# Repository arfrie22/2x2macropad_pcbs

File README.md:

# The PCBs for the 2x2 Macropad

This is a 2x2 Macropad with per-key RGB backlighting. It uses the RP2040 microcontroller and uses a custom firmware located at [https://github.com/arfrie22/2x2macropad_firmware](https://github.com/arfrie22/2x2macropad_firmware).

The PCBs are designed in KiCad

## Features

- Custom lighting effects
- Support for normal keys and media keys
- Keys can act as a key or used for a custom macro
- Up to 4 macros per key
- Customizable timing

## Building

The interactive BOM is can be viewed [here](https://htmlpreview.github.io/?https://raw.githubusercontent.com/arfrie22/2x2macropad_pcbs/main/pcb/bom/ibom.html).

There are 3 pcbs in this project:

- The main pcb, which contains all of the components
- The top plate, which holds the keyswitches
- The bottom plate, which protects the components

## Info

This project was created for a workshop hosted by the UMass All Campus Makerspace. The keyboard was designed to have as many parts as I could reasonably have be though-hole, while keeping the cost relativly low.

## Pictures

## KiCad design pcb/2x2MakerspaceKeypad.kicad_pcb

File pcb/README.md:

# Macropad pcb

## Images

### Front

### Back

This is the main pcb for the 2x2 Macropad. Everything is on this pcb.
You can find the build instructions [here](https://htmlpreview.github.io/?https://raw.githubusercontent.com/arfrie22/2x2macropad_pcbs/main/pcb/bom/ibom.html).

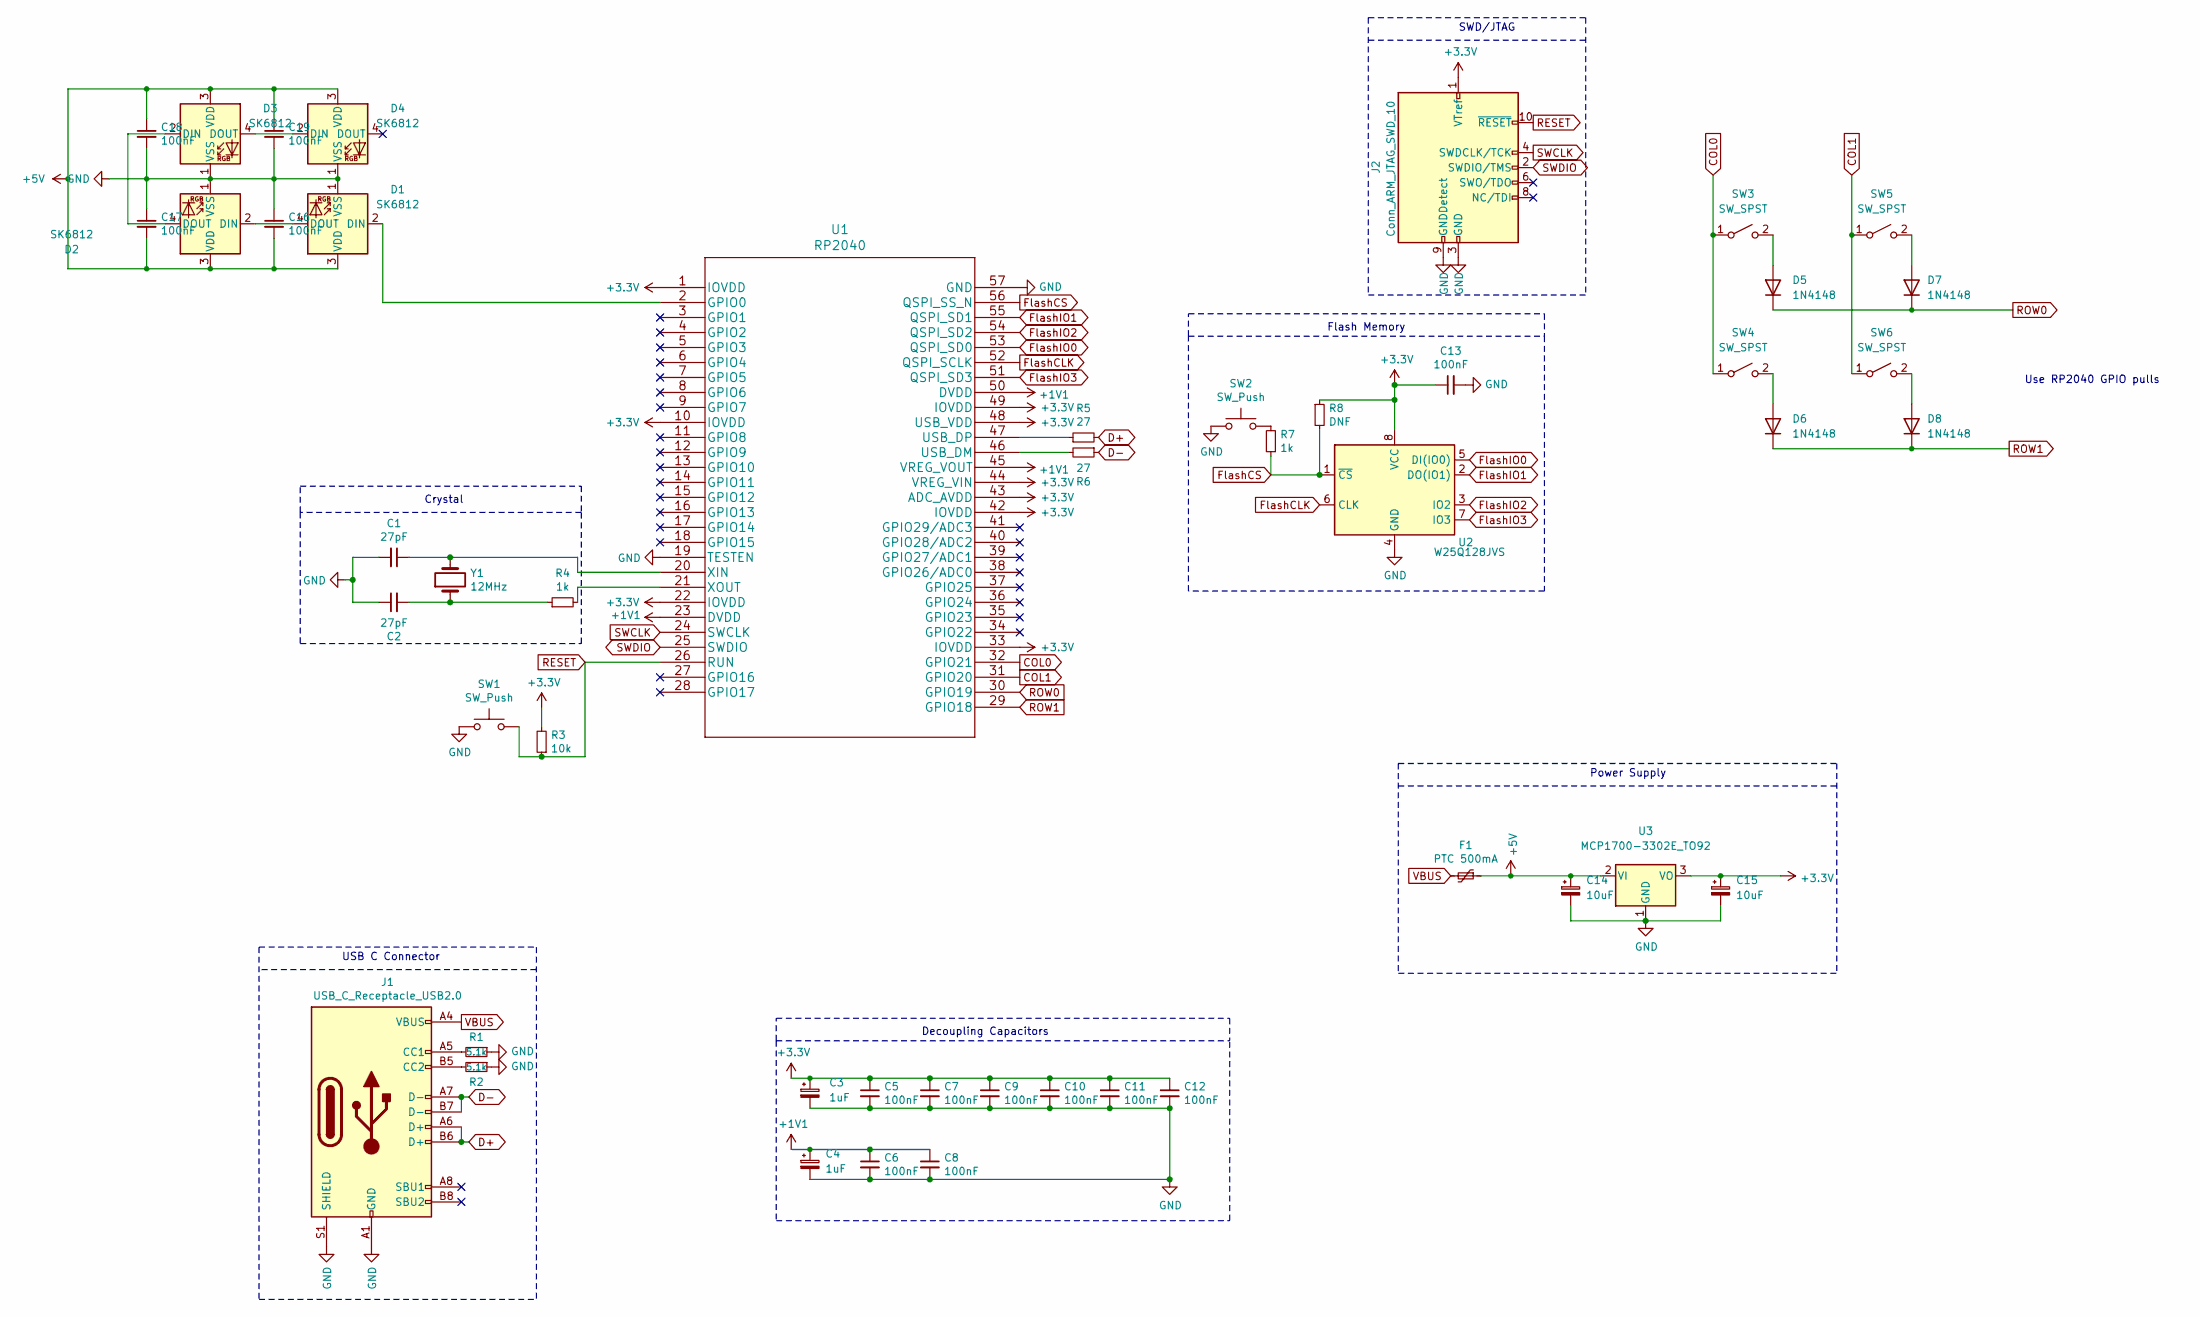
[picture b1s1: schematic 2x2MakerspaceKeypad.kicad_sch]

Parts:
C1, C2: 27pF; C_Disc_D5.0mm_W2.5mm_P5.00mm
C3, C4: 1uF; C_0402_1005Metric_Pad0.74x0.62mm_HandSolder
C5, C6, C7, C8, C9, C10, C11, C12, C13, C16, C17, C18, C19: 100nF; C_0603_1608Metric_Pad1.08x0.95mm_HandSolder
C14, C15: 10uF; CP_Radial_D5.0mm_P2.00mm
D1, D2, D3, D4: SK6812; SK6812-MINI-E-mx
D5, D6, D7, D8: 1N4148; D_DO-35_SOD27_P7.62mm_Horizontal
F1: PTC 500mA; Fuse_1206_3216Metric_Pad1.42x1.75mm_HandSolder
J1: USB_C_Receptacle_USB2.0; USB_C_Receptacle_HRO_TYPE-C-31-M-12
J2: Conn_ARM_JTAG_SWD_10; PinHeader_2x05_P2.54mm_Vertical
R1, R2: 5.1k; R_Axial_DIN0204_L3.6mm_D1.6mm_P5.08mm_Horizontal
R3: 10k; R_Axial_DIN0204_L3.6mm_D1.6mm_P5.08mm_Horizontal
R4, R7: 1k; R_Axial_DIN0204_L3.6mm_D1.6mm_P5.08mm_Horizontal
R5, R6: 27; R_0402_1005Metric_Pad0.72x0.64mm_HandSolder
R8: DNF; R_0603_1608Metric_Pad0.98x0.95mm_HandSolder
SW1, SW2: SW_Push; SW_PUSH_6mm_H5mm
SW3, SW4, SW5, SW6: SW_SPST; SW_Cherry_MX_PCB_1.00u
U1: RP2040; RP2040-QFN-56
U2: W25Q128JVS; SOIC-8_5.23x5.23mm_P1.27mm
U3: MCP1700-3302E_TO92; TO-92_Inline
Y1: 12MHz; Crystal_HC49-4H_Vertical

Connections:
+1V1: C4.1, C6.1, C8.1, U1.23 (DVDD), U1.45 (VREG_VOUT), U1.50 (DVDD)
+3V3: C3.1, C5.1, C7.1, C9.1, C10.1, C11.1, C12.1, C13.1, C15.1, J2.1 (VTref), R3.2, R8.1, U1.1 (IOVDD), U1.10 (IOVDD), U1.22 (IOVDD), U1.33 (IOVDD), U1.42 (IOVDD), U1.43 (ADC_AVDD), U1.44 (VREG_VIN), U1.48 (USB_VDD), U1.49 (IOVDD), U2.8 (VCC), U3.3 (VO)
+5V: C14.1, C16.2, C17.2, C18.1, C19.1, D1.3 (VDD), D2.3 (VDD), D3.3 (VDD), D4.3 (VDD), F1.1, U3.2 (VI)
COL0: SW3.1 (A), SW4.1 (A), U1.32 (GPIO21)
COL1: SW5.1 (A), SW6.1 (A), U1.31 (GPIO20)
D+: J1.A6 (D+), J1.B6 (D+), R5.2
D-: J1.A7 (D-), J1.B7 (D-), R6.1
FlashCLK: U1.52 (QSPI_SCLK), U2.6 (CLK)
FlashCS: R7.1, R8.2, U1.56 (QSPI_SS_N), U2.1 (~CS)
FlashIO0: U1.53 (QSPI_SD0), U2.5 (DI(IO0))
FlashIO1: U1.55 (QSPI_SD1), U2.2 (DO(IO1))
FlashIO2: U1.54 (QSPI_SD2), U2.3 (IO2)
FlashIO3: U1.51 (QSPI_SD3), U2.7 (IO3)
GND: C1.2, C2.1, C3.2, C4.2, C5.2, C6.2, C7.2, C8.2, C9.2, C10.2, C11.2, C12.2, C13.2, C14.2, C15.2, C16.1, C17.1, C18.2, C19.2, D1.1 (VSS), D2.1 (VSS), D3.1 (VSS), D4.1 (VSS), J1.A1 (GND), J1.A12 (GND), J1.B1 (GND), J1.B12 (GND), J1.S1 (SHIELD), J2.3 (GND), J2.5 (GND), J2.9 (GNDDetect), R1.1, R2.1, SW1.1, SW2.1, U1.19 (TESTEN), U1.57 (GND), U2.4 (GND), U3.1 (GND)
unnamed: C1.1, U1.20 (XIN), Y1.2
unnamed: C2.2, R4.1, Y1.1
unnamed: D1.2 (DIN), U1.2 (GPIO0)
unnamed: D1.4 (DOUT), D2.2 (DIN)
unnamed: D2.4 (DOUT), D3.2 (DIN)
unnamed: D3.4 (DOUT), D4.2 (DIN)
unnamed: D5.2 (A), SW3.2 (B)
unnamed: D6.2 (A), SW4.2 (B)
unnamed: D7.2 (A), SW5.2 (B)
unnamed: D8.2 (A), SW6.2 (B)
unnamed: J1.A5 (CC1), R1.2
unnamed: J1.B5 (CC2), R2.2
unnamed: R4.2, U1.21 (XOUT)
unnamed: R5.1, U1.47 (USB_DP)
unnamed: R6.2, U1.46 (USB_DM)
unnamed: R7.2, SW2.2
RESET: J2.10 (~RESET), R3.1, SW1.2, U1.26 (RUN)
ROW0: D5.1 (K), D7.1 (K), U1.30 (GPIO19)
ROW1: D6.1 (K), D8.1 (K), U1.29 (GPIO18)
SWCLK: J2.4 (SWDCLK/TCK), U1.24 (SWCLK)
SWDIO: J2.2 (SWDIO/TMS), U1.25 (SWDIO)
VBUS: F1.2, J1.A4 (VBUS), J1.A9 (VBUS), J1.B4 (VBUS), J1.B9 (VBUS)

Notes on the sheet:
Crystal
SWD/JTAG
USB C Connector
Use RP2040 GPIO pulls
Flash Memory
Decoupling Capacitors
Power Supply

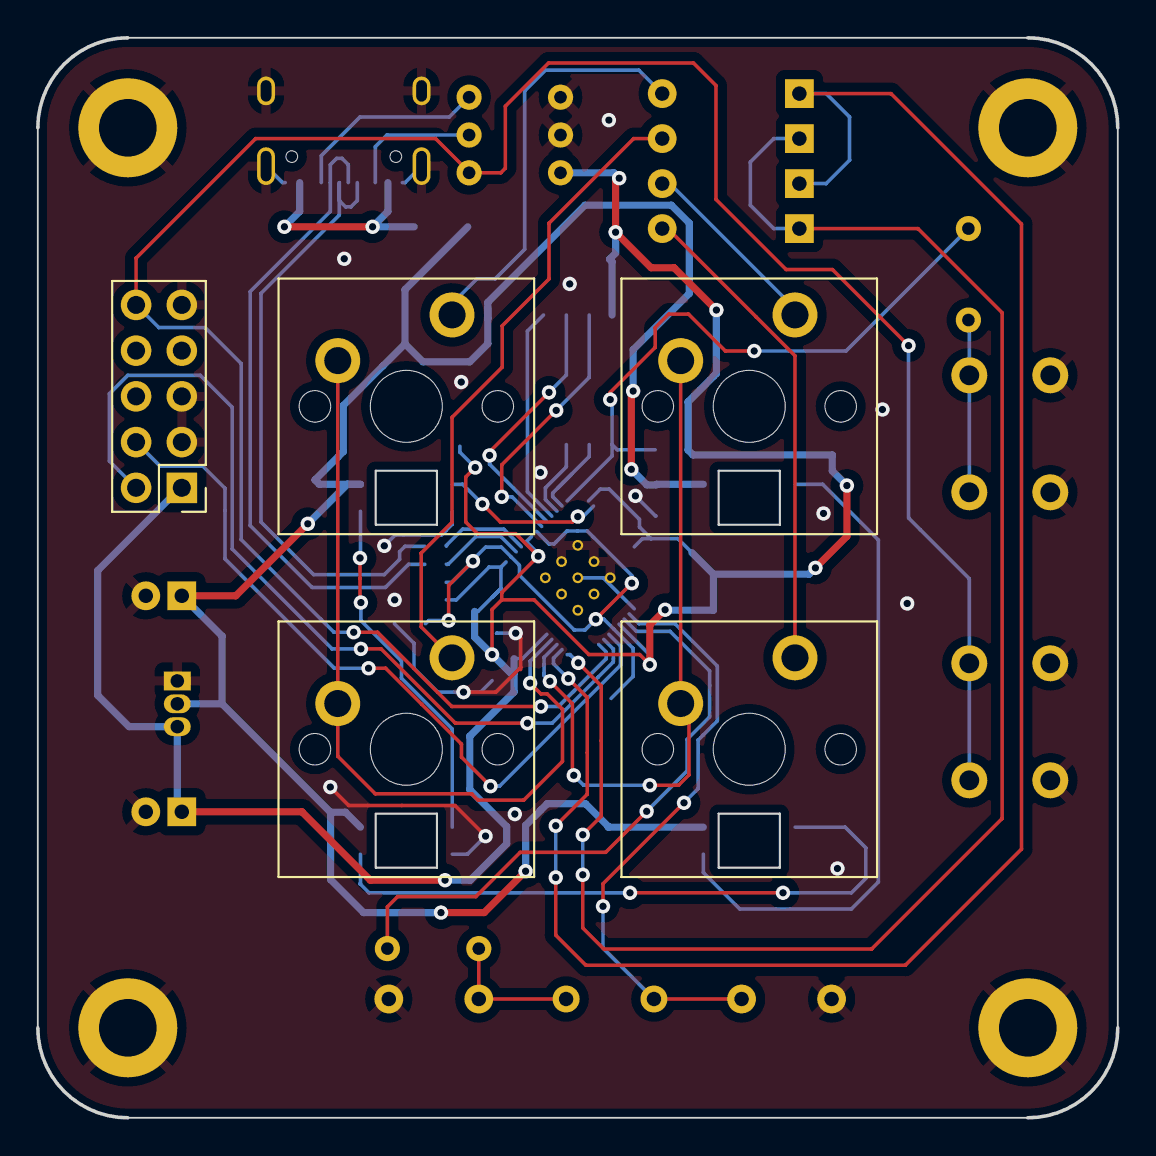
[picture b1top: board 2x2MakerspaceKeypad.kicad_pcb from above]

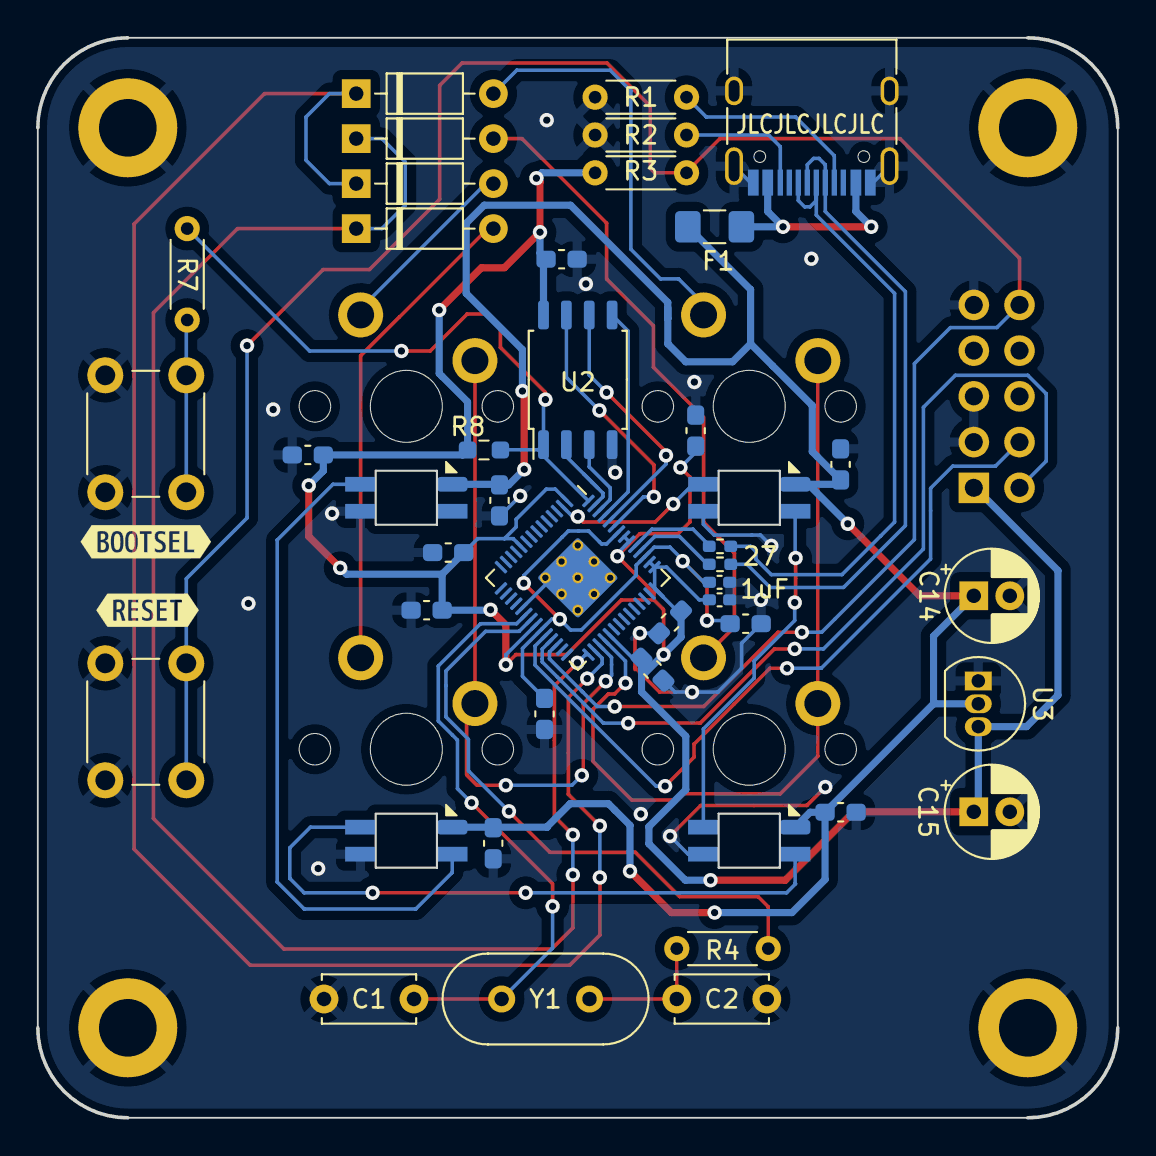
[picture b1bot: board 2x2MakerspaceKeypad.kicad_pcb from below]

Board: 2 copper layers, 60.0 x 60.0 mm, 50 parts (45 on the bottom side), 36 nets.

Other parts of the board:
kibuzzard-6390E1A9: G***; kibuzzard-6390E1A9
kibuzzard-6390E1BA: G***; kibuzzard-6390E1BA

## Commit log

2023-01-07 Added macropad v2
2023-02-09 Added readme + kikit files
2023-02-09 added readmes
2023-02-09 added readme for scripts
2023-02-10 added bom
2023-02-10 fixed readme
2023-02-15 Updated stencil jig
2023-02-15 added images and a bit of info to readme
2023-02-15 added another image
